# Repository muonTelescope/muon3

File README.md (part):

# Muon3: a networked cosmic-ray muon station

**In plain English:** muons from cosmic-ray showers pass through us all the time. A plastic scintillator tile gives off a
tiny flash when one crosses it. A silicon photomultiplier (SiPM) turns that flash into a current pulse, and a small board
counts pulses that arrive in several stacked tiles at once. Muon3 is the next-generation station for the Georgia State
University [gLOWCOST](https://cosmic.gsu.edu/) network: cheap, identical detectors in classrooms and labs that log how the
muon rate follows air pressure, temperature and space weather.

A station is **four decommissioned sPHENIX inner-HCal tiles** (Hamamatsu S12572-33-015P SiPMs), stacked 100 mm apart in a
printed ABS frame. Each tile carries one wavelength-shifting fiber in a closed loop, under a reflective coating and a
light-tight wrap. **One 337 × 40 mm, 4-layer, USB-powered board**, assembled by JLC on one side, stands behind the tiles with
its long axis along the stack: its four channel cells sit right behind the four SiPM boards, so the four micro-coax cables are
short (57 mm) and identical. The hub (USB-C, ESP32, bias supply, pressure/temperature) sits between tiles 1 and 2. A printed
three-segment case covers the board. There is no display: the station reports over USB and Wi-Fi.

| | |
|---|---|
|  |  |

## Contents

0. [Quick start](#quick-start) · [How a muon becomes a count](#how-a-muon-becomes-a-count) · 1. [What you get](#1-what-you-get) · 2. [Bill of materials and cost](#2-bill-of-materials-and-cost) · 3. [Install it: step by step](#3-install-it-step-by-step)
· 4. [Test and calibrate](#4-test-and-calibrate) · 5. [The 12 tile shapes](#5-the-12-tile-shapes) · 6. [The electronics](#6-the-electronics)
· 7. [Simulated performance](#7-simulated-performance) · 8. [Regenerate the design files](#8-regenerate-the-design-files)
· 9. [The bench test board](#9-the-bench-test-board) · 10. [Wright-style detector layouts](#10-wright-style-detector-layouts)
· 11. [Design notes, open questions, repository map](#11-design-notes-open-questions-repository-map)

---

## Quick start

```bash
git clone git@github.com:muonTelescope/muon3.git && cd muon3/hw
bun run parts && bun run build && bun run drc      # the board: Gerbers, BOM, CPL in hw/out/ (section 8 lists the tools to install first)
freecadcmd case/case.py                            # the three case segments
TILE=6 freecadcmd case/assembly.py                 # the frame, plate and tile stack for tile shape 6 (any of 1–12)
python tools/station_test.py board                 # factory test over USB, once a board is assembled
```

## How a muon becomes a count

1. **Light.** A cosmic-ray muon crossing a 7 mm polystyrene tile deposits about 1.5 MeV and makes some 13 000 scintillation photons
   (blue, 420 nm). About 2 500 of them are absorbed by the 1 mm wavelength-shifting fiber in the tile and re-emitted at 476 nm (green);
   light trapped in the fiber travels both ways round the closed loop to the SiPM. Of the order of 150 photons reach the SiPM and about
   35 are detected (PDE 25 %): the **photoelectrons (p.e.)**.
2. **Current.** The S12572 SiPM, biased at 53–83 V, turns each p.e. into a fast current pulse (gain about 2.3 × 10⁵). The bias comes from
   the MC34063 boost converter on the board and reaches the SiPM over the same micro-coax that carries the signal back.
3. **Voltage.** A transimpedance amplifier (OPA356, 33 kΩ) gives 5.8 mV per p.e., so a mean muon makes a 209 mV pulse about 370 ns long.
4. **Decision.** A comparator (LMV7219) fires when the pulse passes a threshold set by a DAC: 29 mV, 5 p.e., rejects dark counts (single
   p.e.) and keeps essentially every muon that crosses the tile.
5. **Count.** The ESP32-S3 time-stamps each edge (MCPWM capture, 12.5 ns) and counts singles (PCNT); coincidences of the four tiles are
   formed in firmware, together with pressure and temperature (BME280), and sent over Wi-Fi or USB. The muon rate follows air pressure,
   temperature and space weather: that is what the gLOWCOST network logs. `sim/python/coincidence_rates.py` computes the coincidence and
   accidental rates; `sim/python/sipm_to_tot.py` maps SiPM charge to time over threshold.

---

## 1. What you get

- **Identical channels.** Channel 0 is placed and routed once; cells 1–3 are exact copies at a 100 mm pitch (copper identical
  to 2 µm, checked on every build with `hw/tools/cell_identity.py`). The pitch is the tile pitch, so cell *k* is behind tile *k*.
- **The SiPM bias never leaves the case.** Each tile's micro-coax plugs into a U.FL jack inside the case.
- **External antenna.** An ESP32-S3-WROOM-1U-N16R8 sends its Wi-Fi/BLE through a U.FL pigtail to a flat antenna on the lid.
- **Fits every tile.** All 12 inner-HCal tile shapes, from the 121 mm wide, nearly rectangular tile 01 to the 403 mm
  parallelogram tile 12, get a frame and a fiber loop generated from their outline.
- **Self-testing.** The board tests itself over USB in 2 minutes (nothing plugged in), and calibrates each tile's gain from its
  own dark counts.

```text
 tile ─ micro-coax ─► U.FL in the case (shell = bias via 47 kΩ) ─► OPA356 TIA (33 kΩ ‖ 2.7 pF) ─► LMV7219 ─► HIT_n ─► ESP32-S3
   ×4 (identical cells)           ▲                               ▲ VREF (DAC B·A)             ▲ VTH_n (DAC A)      PCNT + MCPWM
             MC34063 boost → 10 k / 1 µF RC ─ HV (53–83 V) ◄─ HV_TRIM (DAC B·B) ◄──────────────────────────── HV_EN
                         └──────────── HV_MON (÷ 27.7) ────────────────────────────────────────────────────► ADC
 INJ (GPIO) ─ 10 k/1.1 k ─ 1 pF into each input: 0.33 pC = 9 p.e. self-test
 BME280 (slotted thermal island, ≥ 20 mm from any input) · SC7A20H tilt · USB-C 5 V → AMS1117 3V3 + TLV75733 3V3A
```

---

## 2. Bill of materials and cost

### Board (JLC assembles it; 155 parts, 45 lines)

Upload `hw/out/muon3-gerbers.zip`, `hw/out/bom.csv` and `hw/out/cpl.csv` to JLCPCB: **4 layers, 1.6 mm, top-side assembly only**,
337 × 40 mm. Parts come from LCSC; the full list is [`hw/parts/INDEX.md`](hw/parts/INDEX.md).

| Line | Part | Per board | Share |
|---|---|---|---|
| BME280 (pressure, temperature) | C92489 | $4.46 | 27 % |
| ESP32-S3-WROOM-1U-N16R8 (Wi-Fi, BLE, U.FL antenna connector) | C3013946 | $4.10 | 24 % |
| MCP4728 DAC × 2 | C478093 | $3.06 | 18 % |
| OPA356 TIA × 4 | C183100 | $1.83 | 11 % |
| LMV7219 comparator × 4 | C20613263 | $0.99 | 6 % |
| U.FL jack × 4, SC7A20H, AMS1117, MC34063, TLV75733 | | $0.95 | 6 % |
| the other 34 lines, mostly 0402/0805 passives | | $1.19 | 7 % |

**Cost at 100 boards (importer: GSU): parts $16.58 + PCB $6.19 + JLC assembly $1.32 = $24.08 ex-works, $35.57 landed in the US**
($105.57 per board for the two Berlin prototypes). The PCB price is an estimate ($0.045 per cm² of 4-layer board, 135 cm² here): get a
quote. Cheaper variants (saves about $6.3 per board, landed $35.6 → $26.4): BME280 → SPA06-003 (same package, pressure + temperature,
$0.51), drop the second MCP4728 (fixed VREF divider, PWM HV trim), ESP32 N4 module, drop the tilt sensor, two extended parts →
basic parts. Not worth it: a 2-layer board (saves $1.50, loses the ground plane), dropping the analog LDO, cheaper op-amps.

### Mechanics and cables (you print and buy these)

| Part | Qty | How |
|---|---|---|
| Corner clip (ABS, 12.4 mm thick, 8.0 mm slot, M6 hole) | 16 | printed, flat |
| Spacer tube (Ø 12 / Ø 6.4) | 18 (6 × 87.6 mm, 12 × 4.8 mm) | printed; the long ones can be aluminium tube |
| Back plate bar (one piece for tiles 1–11; two halves + a splice plate for tile 12) | 3 | printed, lying on its back |
| Case base + lid, segments A (71 mm), B (200 mm), C (71 mm) | 3 + 3 | each flat |
| M6 threaded rod, about 345 mm | 4 | cut from 1 m stock |
| M6 nut + washer | 8 + 8 | |
| M3 × 5.7 heat-set insert | 13 (lid) + 10 (plate bars) (+ 12 for the tile-12 splices) | pressed in with a soldering iron |
| M3 × 12 socket-head screw (ISO 4762) | 13 | lid, through the board's edge holes |
| M3 × 6 socket-head screw (ISO 4762) | 10 (+ 12 for the tile-12 splices) | case floor to plate bars |
| U.FL to U.FL micro-coax, Ø 1.13 mm, 70 mm | 4 | tile SiPM board to station board; four equal lengths |
| 2.4 GHz FPC antenna, 35 × 7 mm, with U.FL pigtail | 1 | sticks in the lid recess |
| Tile wrap: 100 µm Al foil, 30 µm cling film, 100 µm black vinyl, epoxy (EPO-TEK 301 class) | 4 tiles | plus the tile's 50 µm painted reflector |
| 4 decommissioned sPHENIX inner-HCal tiles with their fibers, SiPMs and SiPM boards (from GSU) | 4 | of one shape |

Print in ABS at 0.2 mm layers, 4 perimeters, 30 % infill, 100 °C bed, enclosure closed. The longest parts are case segment B
(206 mm) and the plate bars (up to 212 mm): both fit a 220 mm bed.

---

## 3. Install it: step by step

All M3 joints are **socket-head screws into heat-set inserts** (no nuts, no glue). Press the inserts in first: hold each on its hole
with a soldering iron at 220–240 °C and push it flush. Everything below is generated for your tile shape (1–12): run the commands in
[section 8](#8-regenerate-the-design-files) with `TILE=<n>` to get the exact STL/STEP files.

### Step 0: order and print

1. Order the board (section 2). Order or print the parts (`hw/out/case/case_{base,lid}_{A,B,C}.stl`, and the clips, spacers and bars
   from `hw/out/assembly/tileNN/`).
2. Check the board when it arrives: `python hw/tools/station_test.py board` (section 4).

### Step 1: the tiles

The tile is a slab of extruded polystyrene with **one Kuraray Y11 fiber laid in a closed loop**: both ends leave the flat SiPM edge
side by side, each runs through an S-bend of 25 mm radius onto a leg, the two legs run down the tile and a semicircle closes the
loop near the far edge. Over the tile go the **50 µm painted reflector** and the **wrap: 100 µm aluminium foil, 30 µm cling film,
100 µm black vinyl**, each following the tile's outline and open only where the coupler sits (Aidala et al., IEEE TNS 65 (2018),
Table II and Fig. 6). Tiles 01, 06 and 12, bare, with the fiber in its groove and the coupler and SiPM board on the SiPM edge:

The same tile with its layers lifted off one by one (reflector, foil, cling film, vinyl):

1. Lay the fiber in its groove (epoxy) and cut and polish both ends flush with the SiPM edge.
2. Put on the reflector and the wrap (foil, cling film, vinyl), open at the coupler.
3. Glue the coupler block (16 × 6 × 8 mm, black ABS) on the SiPM edge over the two fiber ends, with the SiPM board and its U.FL
   jack behind it. Both ends, 1.2 mm apart, face the one 3 × 3 mm SiPM across a 0.75 mm air gap.

### Step 2: the frame

Slide the four rods through the bottom clips, add the nuts, then build up: spacer, tile in its four corner clips, spacer, next tile.
The four clips of a tile clamp its corners in an 8.0 mm slot; the tile is never drilled. The rods sit 8.5 mm outside each corner, so
they never touch the scintillator.

### Step 3: the back plate

A bar replaces the back-rod spacer between tiles 0/1, 1/2 and 2/3. Each bar's two sleeves slide onto the back rods (bars are at
z = 50, 150 and 250 mm, clear of the SiPM boards at z = 0, 100, 200, 300, so the coax passes between them). For tile 12 each bar is
two halves joined by a splice plate on the front face (4 × M3 × 6).

### Step 4: the electronics

Press the inserts into the three case bases. Drop the board onto the bosses of the bases (the board's underside has no parts; the
heads of the floor screws sit in the 4.6 mm gap under it), close the three lids (13 × M3 × 12) and screw each segment's base to the
bars (10 × M3 × 6). The segments join at the bars (board x = 68.5 and 268.5 mm). The USB-C opening is on the far long wall, the
BME280 vent beside it.

### Step 5: cables and antenna

Plug a 70 mm micro-coax onto each tile's SiPM board, route it out to the case wall, and click its other plug onto the board's jack
through the notch in the lid skirt, then lay it in the zip-tie bridge on the wall. All four cables are identical. Stick the FPC antenna
in the lid recess and click its pigtail onto the ESP32 module's U.FL through the lid hole.

### Sections (tile 01)

Through the SiPM edge (scintillator with its coating and wrap, fiber in its groove, coupler, SiPM, board, plug) and through the case
at the hub (lid, board on its 4.6 mm standoffs, base, plate bar):

| | |
|---|---|
|  |  |

The widest shape (tile 12), from the back:

### Case and plate details

- **Three printed segments** (71, 200, 71 mm, each with a base and a lid, split at the board mid-plane) because the board is 337 mm long;
  the joints sit on the plate bars. The lid screws sit 7 mm either side of a joint so that no boss is cut.
- **Coax entry.** A 1.8 × 2.4 mm notch in the lid skirt above each U.FL takes the micro-coax; a small zip-tie bridge on the wall takes the
  strain off the plug. The bias on the U.FL shells stays inside the closed case.
- **BME280 chamber.** Ribs above and below the island (stopping 0.15 mm short of the board), vented to room air through eight 1.6 mm
  slots in the far wall. **Hot side:** eight 1.6 × 14 mm chimney slots in the floor and lid over the ESP32 and AMS1117.
- **External antenna.** A Ø 3.2 mm hole in the lid over the module's U.FL jack passes the pigtail to a 35 × 7 × 0.7 mm recess on the
  lid's outer face, along the far edge.
- **Mounting.** Ten Ø 3.4 mm holes in the base floors take M3 × 6 screws into the bars' inserts (two per segment per bar).

### Step 6: install

Put the stack where it will stay (tiles horizontal). Plug a USB-C power source into the hub's USB-C port (a bank that can deliver
the station's 40–120 mA continuously: many switch off below 50–100 mA). Give it Wi-Fi credentials over the USB serial port.
*(The firmware is not written yet: its USB line protocol is specified in `hw/tools/station_test.py`.)*

---

## 4. Test and calibrate

Every board is tested and calibrated by the ESP32 itself, driven from a laptop over USB:

```bash
python hw/tools/station_test.py board          # factory test: nothing plugged in, about 2 min
python hw/tools/station_test.py tile --ch 0    # per tile, at installation: about 10 min per channel
```

No scope or fixture is needed. The probe row (22 pads, 2.54 mm pitch, far long edge at the right-hand end of the board) and the
TIA/GND scope pair in each channel cell are for diagnosing a board that fails. The station has one status LED (next to the BOOT
button, through a light pipe in the lid): the firmware is specified to blink fast during the 10 s self-test, slowly while counting and
to stay on in a fault.

**How it works.** Each channel has a 1 pF injection capacitor driven from the INJ GPIO through a 10 k / 1.1 k divider: each edge puts
0.33 pC on the TIA input, which is 9 photoelectrons (p.e.). The firmware sweeps the threshold DAC and counts HIT pulses: the threshold
at which half the injected pulses still fire measures the whole chain at once. The bias checks itself through HV_MON (HV ÷ 27.7). The
tile calibrates its own gain: in the dark a SiPM fires single p.e., the count rate against threshold falls in a staircase, and the step
spacing is 1 p.e. (set the bias so it is 5.8 mV, then put the threshold at 5 p.e. = 29 mV). The same staircase, repeated every few
minutes, is the running gain servo.

### Factory test (`board`)

| Step | What the firmware does | Pass | Source |
|---|---|---|---|
| 1 | Scan both I2C buses | BME280 0x76, SC7A20H 0x19, MCP4728 0x60 on I2C0 and I2C1 | design |
| 2 | Read BME280 pressure | 850–1090 hPa | — |
| 3 | HV_EN low, read HV_MON | 2.5–5.5 V (USB 5 V minus the boost diode; not 0 V) | [SIM] ≈ 4 V |
| 4 | HV_EN high, TRIM = 0 / 1.0 / 2.048 V | 80–86.5 V / 65.5–71.5 V / 50–56 V | [SIM] 83.0 / 68.3 / 52.9 V |
| 5 | Store HV(TRIM) line; leave the bias at TRIM 2.048 V and HV_EN low | — | — |
| 6 | Per channel: VTH staircase with no injection | noise edge ≤ 8 mV below VREF | [SIM] < 3 mV |
| 7 | Per channel: VTH staircase with INJ pulses, 50 % point | 85–135 mV below VREF | [SIM] 109 mV |
| 8 | Join the test access point, read RSSI (the external antenna must be on the lid) | ≥ −65 dBm at 2 m | first prototype |

*Simulated scope screens (what you should see on the probe points): ① injection with nothing plugged in: a 109 mV dip follows each INJ
edge and HIT0 fires on the negative one. ② With a tile and coax attached the charge shares the SiPM's 320 pF and the dip halves (55 mV).
③ A single dark pulse (5.8 mV, shown ×10) and a mean muon (36 p.e., 209 mV, time over threshold ≈ 370 ns). ④ The bias power-up on
HV_MON: ≈ 4 V until HV_EN goes high at 10 ms, then 60–90 ms to settle.*

### Per-tile calibration (`tile`)

1. Attach the tile and close the light-tight wrap. Set the bias to the tile's operating voltage V_op (from the Hamamatsu/GSU sheet);
   the firmware closes the loop on HV_MON using the stored HV(TRIM) line.
2. **Staircase.** Sweep VTH 1–40 mV below VREF, 200 ms per step. The peaks in −d(log rate)/dVTH sit between p.e. steps; their
   spacing is the 1 p.e. amplitude.
3. If the step is not 5.8 mV, move V_op by ΔV = (5.8 / step − 1) · (V_op − V_bd) and repeat.
4. Threshold = 5 p.e.; store `pe_n`, `vth_n` and V_op in NVS.
5. With the tiles stacked, run the coincidence plateau: V_op ± 1 V in 0.25 V steps, 5 min each. The rate should be flat within its
   statistical error. Expect a few counts per minute for a 12 × 19 cm tile (cosmic muons: about 1 per cm² per minute × the geometric
   acceptance). Measure each tile's efficiency with the coincidence method (three tiles fire, does the fourth?).

### Diagnosing a failed board

| Probe (row, left → right) | Expect |
|---|---|
| GND · 5V · 3V3 · 3V3A | 0 · 4.8–5.2 · 3.25–3.35 · 3.25–3.35 V |
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
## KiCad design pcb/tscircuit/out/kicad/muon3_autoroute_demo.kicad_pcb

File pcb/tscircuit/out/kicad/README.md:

# Muon3 tscircuit → KiCad export

Generated by `bun run export:kicad` from `muon3_placement.tsx`.

## Files

| File | Use |
|------|-----|
| `muon3_tscircuit_placement.kicad_pro` | Open in KiCad 9+ as **placement reference** |
| `muon3_tscircuit_placement.kicad_pcb` | Footprints, keepouts, zone silkscreen from tscircuit |
| `muon3_tscircuit_placement.kicad_sch` | Minimal schematic (placement anchors only) |
| `../placement_positions.json` | Component XY for manual placement in production PCB |
| `../placement_positions.csv` | Same table as CSV |

## How to use with production `muon3.kicad_pro`

1. Open **this** project to inspect recommended placement / keepouts.
2. Open **`../../muon3.kicad_pro`** (hierarchical production sheets).
3. Place production footprints using `placement_positions.csv` coordinates
   (KiCad columns), or run `bun run sync:zones` to stamp zone fences into
   the production board outline.
4. For autorouted demo nets → KiCad, run `bun run autoroute` then re-export.

**Do not** overwrite production hierarchical schematics with this export.

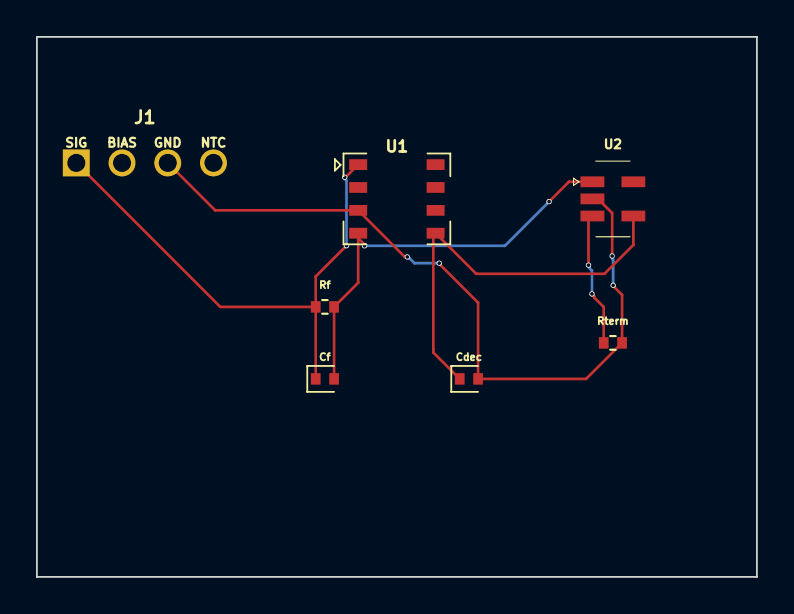
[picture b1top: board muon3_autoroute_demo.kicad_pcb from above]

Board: 2 copper layers, 40.0 x 30.0 mm, 7 parts (0 on the bottom side), 5 nets.

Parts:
Cdec: 100nF; capacitor_0402
Cf: 1pF; capacitor_0402
J1: chip_pinrow4
Rf: 4.99kΩ; resistor_res0402
Rterm: 49.9Ω; resistor_res0402
U1: chip_dfn8
U2: chip_sot23_5

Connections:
.J1 > .pin1 to .U1 > .pin1: Cf.1, J1.1, Rf.1, U1.1
.Rf > .pin2 to .U1 > .pin4: Cf.2, Rf.2, U1.4, U2.1
.U2 > .pin3 to .Rterm > .pin1: Rterm.1, U2.3
GND: Cdec.2, J1.3, Rterm.2, U1.3, U2.2
VCC_3V3: Cdec.1, U1.5, U2.4

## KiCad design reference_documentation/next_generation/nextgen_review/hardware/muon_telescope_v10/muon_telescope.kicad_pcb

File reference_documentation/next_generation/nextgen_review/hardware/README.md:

# SiPM Muon Telescope — KiCad Project (KiCad 10)

Generated 2026-06-11. Four hierarchical sheets implementing the simulated TIA front-end design
(see the accompanying simulation report): 4× SiPM → OPA858 TIA → TLV3601 → iCE40UP5K-SG48,
TPS61170 HV boost + π filter + DAC trim + ADC readback, DAC7578 thresholds, BME280, W25Q128
config flash, TCXO, GNSS-module and nRF9151-carrier headers.

## Opening in KiCad 10

Open `muon_telescope_v10/muon_telescope.kicad_pro`. The schematic files are written in the
20250114 s-expression format with generator_version 9.0 — the exact format the KiCad 10.0
release ships its own demo projects in. KiCad 10 opens it natively (the official migration
path); on first save it re-stamps the files to the current 20260306 format. Every s-expression
token used was checked against KiCad 10.0's parser keyword list (eeschema/schematic.keywords,
branch 10.0), and the grammar was pattern-matched against reference files from the 10.0 source
tree.

`muon_telescope_v7/` contains a byte-equivalent-structure twin in KiCad 7 format. It exists
because this project was machine-generated and validated headlessly with kicad-cli 7.0.11:
SVG/PDF plots of all four sheets plus a full netlist export, with the connectivity of every
critical net checked programmatically (TIA feedback loops, all four CMPx→FPGA pins, shared
VBOT, DAC routing, HV trim/readback, PPS, config-flash SPI, nRF SPI, 1V2 core). The v10 set is
generated from the identical structure, so the electrical verification carries over.

## First steps after opening

1. Run ERC. Global-label connectivity is used throughout (machine-generated layout); expect
   only style-level warnings.
2. Annotation is pre-assigned and collision-free; re-annotate only if you restructure.
3. Tidy label positions to taste — symbols are placed on grid but some labels overlap.

## Libraries

- `muon_parts.kicad_sym` — project library, all symbols used. Also embedded in each sheet, so
  the schematics are self-contained.
- `JLCPCB-Kicad-Library/` — bundled subset (symbols + footprints) of
  https://github.com/CDFER/JLCPCB-Kicad-Library (MIT). sym-lib-table and fp-lib-table already
  point at it via ${KIPRJMOD}. Re-clone the upstream repo for 3D models and live stock data.

## Sourcing status (read before ordering)

CDFER basic/preferred parts with LCSC numbers embedded in symbol fields:
all 0402/0603 R and C values, BAV99 (C2500), SS510B 100V Schottky (C7420368), 100µH filter
inductor (C68035), AMS1117-3.3 (C6186), BME280 (C92489), W25Q128JVSIQ (C97521).

Pinout-verified from official KiCad library or TI datasheets, LCSC ID to confirm at order time
(extended parts): OPA858 (WSON-8), TLV3601 (SOT-23-5: 1=OUT 2=VEE 3=IN+ 4=IN− 5=VCC, TI
SNOSDB1E), TPS61170 (VSON-6: 1=FB 2=COMP 3=GND 4=SW 5=CTRL 6=VIN, TI SLVS789D), DAC7578
(TSSOP-16), iCE40UP5K-SG48ITR (QFN-48).

Marked VERIFY in-schematic before ordering: XC6206P122 1.2 V LDO pinout and LCSC number;
TCXO footprint/pinout vs the exact part chosen; the two placeholder LCSC numbers on
0402 1µF / 0603 10µF; DAC7578 I²C address for ADDR0=GND; iCE40 VPP_2V5-from-3V3 against the
current Lattice datasheet; all HV-node capacitors must be ≥50 V (C0G/film on HV_QUIET).

## Design notes carried from simulation

DC-coupled anode readout: SiPM anode sits at the TIA virtual ground (VBOT, 2.40 V), cathode at
HV_QUIET — no input coupling cap, no undershoot. HV ≈ VBOT + Vbr + Vov: ~32.4 V for
MicroFC-30035 as drawn; for Hamamatsu S13360 (~58 V) replace the boost stage, filter unchanged.
Rf=2 kΩ 1%, Cf=2.2 pF C0G → 24.4 mV/p.e., 52 MHz, 3 p.e. threshold = 74 mV below baseline.
Comparator output idles HIGH, pulses LOW (falling edge = event), matching firmware convention.

## Layout-critical items

Rf/Cf at the OPA858 pins, no plane under summing nodes; boost hot loop compact and far from
the four INA nodes; comparator output routing away from analog inputs; star HV_QUIET
distribution after C12; thermal pads (OPA858 pin 9, TPS61170 pin 7, iCE40 pin 49) to GND.

## Regenerating

`python3 gen_sch.py v9` (KiCad-10-ready) or `python3 gen_sch.py v7` (kicad-cli-7-validatable).
gen_symbols.py holds all pin maps with their provenance in comments.

## PCB (muon_telescope.kicad_pcb)

108 x 86 mm, 4-layer: F.Cu signal | In1 solid GND | In2 +3V3 plane | B.Cu GND pour.
Placement complete and DRC-clean (0 clearance / courtyard / hole violations); routing is
intentionally left open — unconnected-net DRC entries are the ratsnest. The board file is
KiCad 7 format; KiCad 10 opens and migrates it like the schematics.

Grounding / noise architecture baked into the file:
- ONE continuous ground domain. No split planes anywhere — return currents cannot be forced
  around a slot, which is the classic ground-loop generator. Partitioning is by placement.
- 31 GND stitching vias on a 9 mm grid keep F.Cu / In1 / B.Cu grounds at the same potential
  at RF, preventing the pour islands from becoming patch antennas.
- Per-channel rule areas (no copper pour, In1+In2+B.Cu) under each TIA summing node:
  keeps parasitic capacitance off the Cf node and leakage paths off the femtocoulomb input.
- Boost quarantine: TPS61170 hot loop bottom-right, >40 mm from the nearest summing node;
  In2 under the entire boost area is GND (priority fill), denying the 3V3 plane any
  capacitive pickup from the switch node directly beneath it.
- U.FL per channel at the board edge: CENTER = anode signal, SHIELD = HV bias. The shield is
  AC-grounded by C1 within ~6 mm of the connector, so it shields normally while DC-carrying
  the bias - one coax per SiPM, minimal loop area. Both shield legs of the BWIPX footprint
  are netted (the upstream CDFER symbol leaves pad 3 floating - fixed here).
- HV netclass (0.5 mm clearance, pattern HV_* + BOOST_SW) is defined in the .kicad_pro.

Routing order suggestion: (1) per-channel input: U.FL center -> R2 -> summing node -> OPA858
pin 3, with Rf/Cf to the FB pin, shortest possible, F.Cu only; (2) TIA -> comparator -> R5;
(3) CMPx to FPGA as spaced single-ended lines over solid In1; (4) HV_QUIET from C12 along the
bottom/left perimeter to the four R1s (DC, filtered - length is free); (5) boost hot loop
L1/U10/D10/C10 tight first, before anything else near it; (6) supplies last via In2 + drops.
Pad-local notes: thermal pads of U10/U101..U131/U3 need via farms to In1.

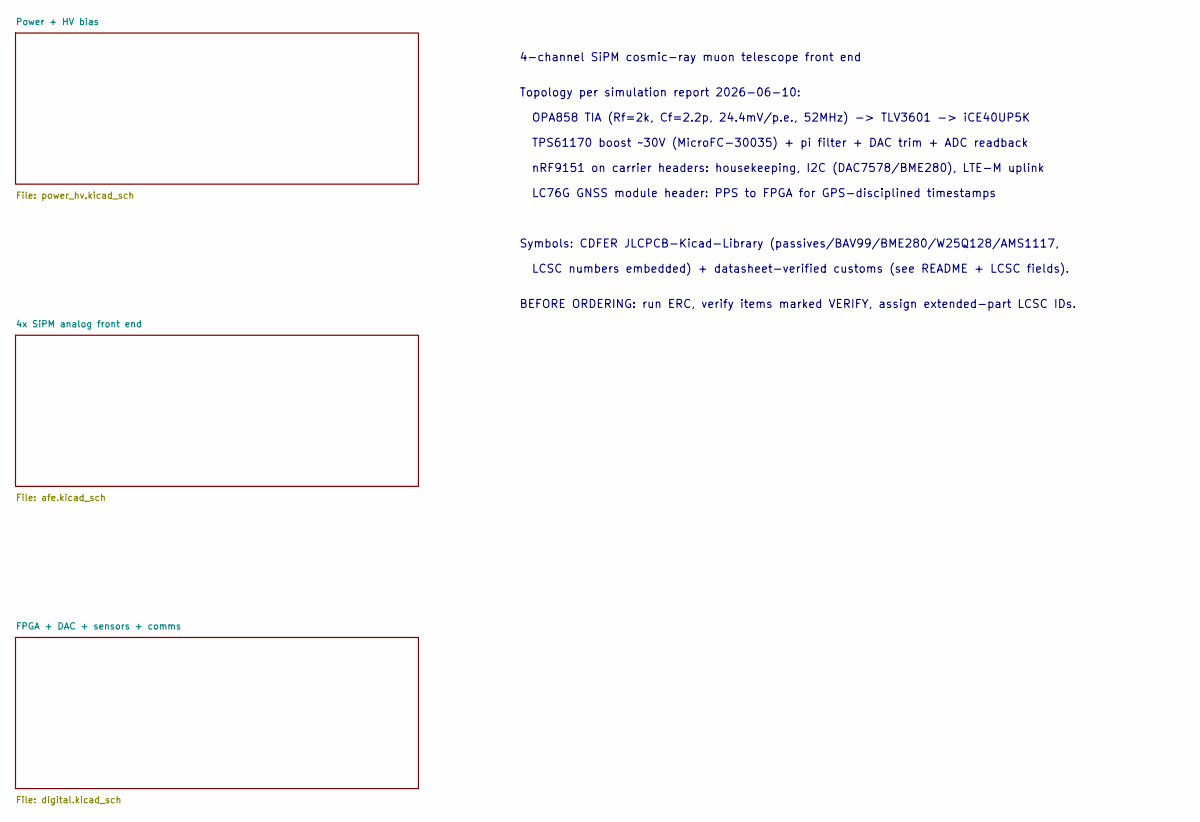
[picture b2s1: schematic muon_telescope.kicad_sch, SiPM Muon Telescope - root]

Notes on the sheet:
4-channel SiPM cosmic-ray muon telescope front end
Topology per simulation report 2026-06-10:
OPA858 TIA (Rf=2k, Cf=2.2p, 24.4mV/p.e., 52MHz) -> TLV3601 -> iCE40UP5K
TPS61170 boost ~30V (MicroFC-30035) + pi filter + DAC trim + ADC readback
nRF9151 on carrier headers: housekeeping, I2C (DAC7578/BME280), LTE-M uplink
LC76G GNSS module header: PPS to FPGA for GPS-disciplined timestamps
Symbols: CDFER JLCPCB-Kicad-Library (passives/BAV99/BME280/W25Q128/AMS1117,
LCSC numbers embedded) + datasheet-verified customs (see README + LCSC fields).
BEFORE ORDERING: run ERC, verify items marked VERIFY, assign extended-part LCSC IDs.

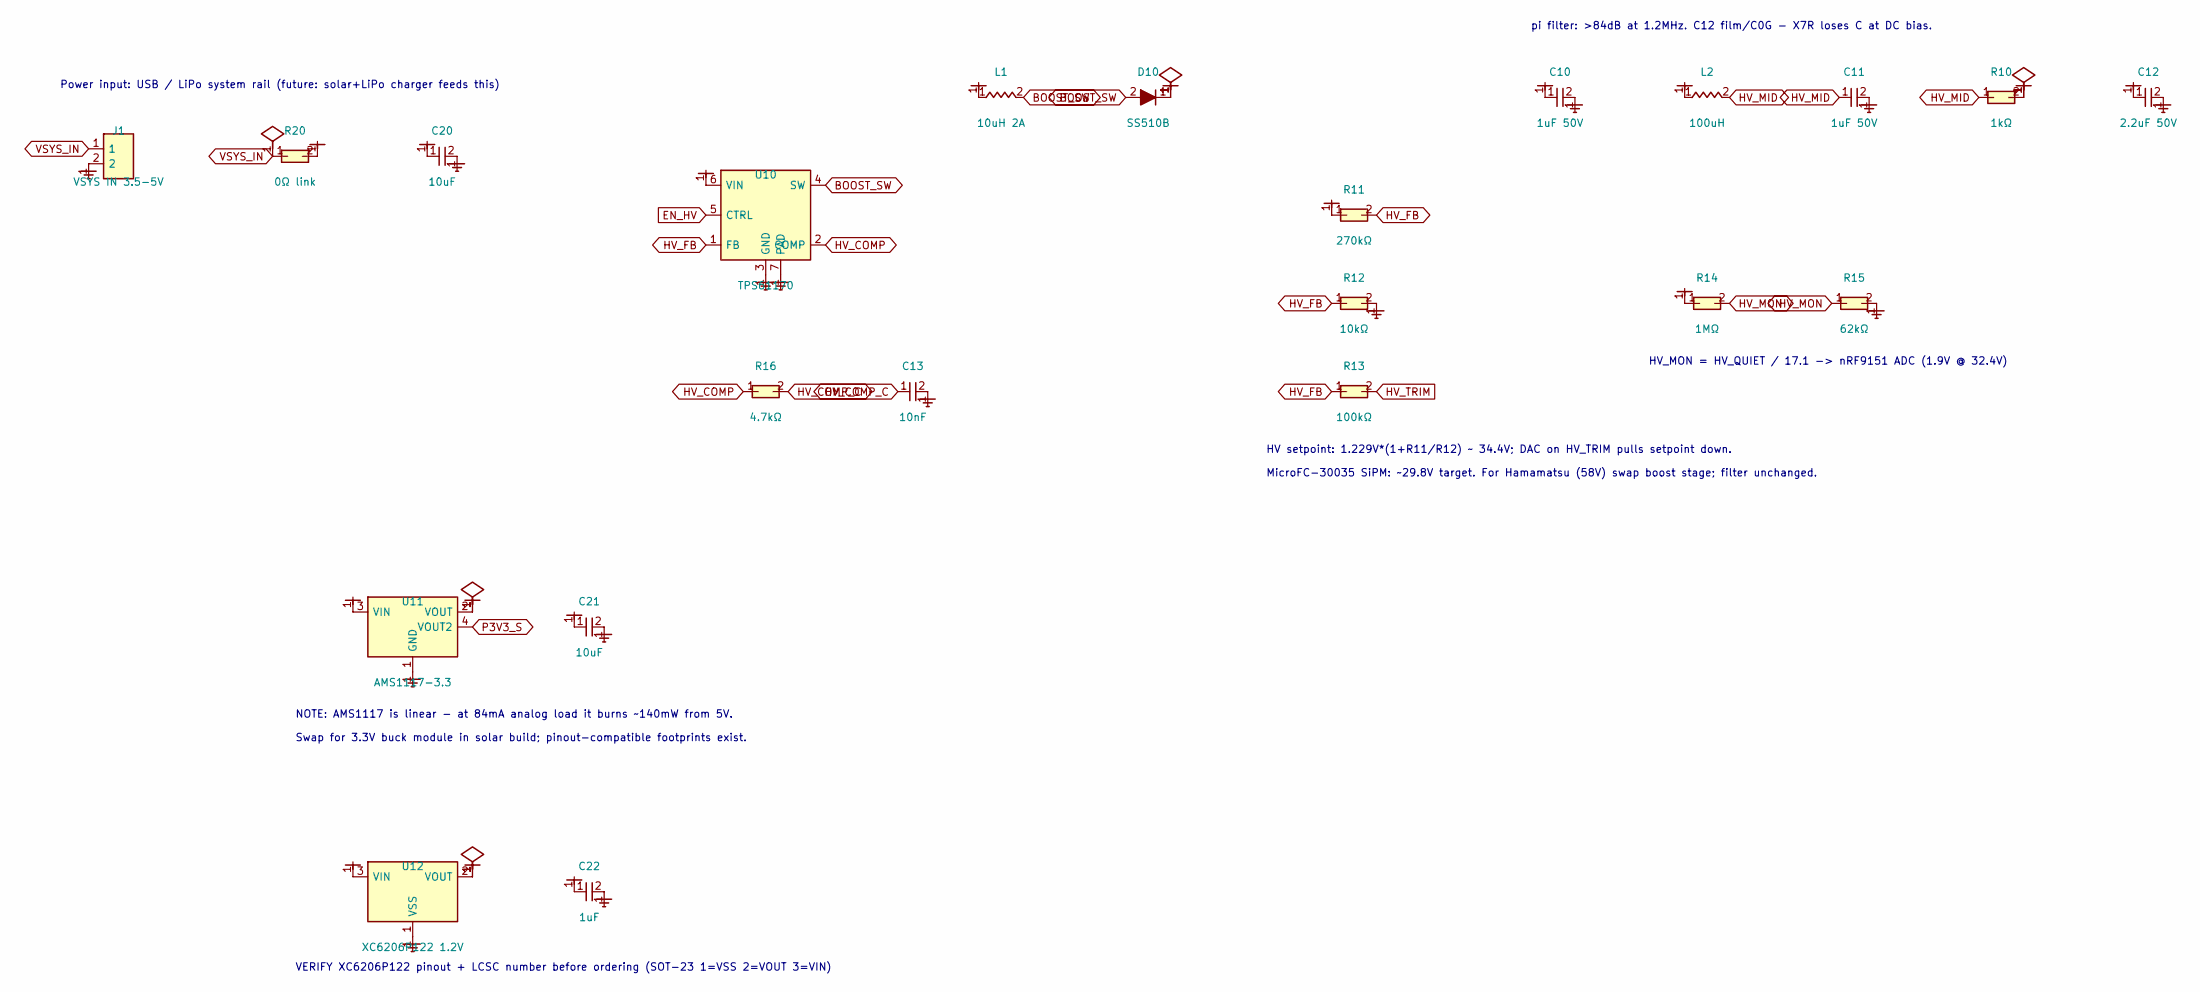
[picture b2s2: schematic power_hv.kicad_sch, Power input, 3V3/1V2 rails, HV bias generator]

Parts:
C10, C11: 1uF 50V; C_1206
C12: 2.2uF 50V; C_1206
C13: 10nF; C_0402; LCSC C15195
C20, C21: 10uF; C_0603; LCSC C19702
C22: 1uF; C_0402; LCSC C52923
D10: SS510B; D_SMB; LCSC C7420368
J1: VSYS IN 3.5-5V; PinHeader_1x02_P2.54mm_Vertical
L1: 10uH 2A; L_Taiyo-Yuden_NR-40xx
L2: 100uH; L_0805; LCSC C68035
R10: 1kΩ; R_0402; LCSC C11702
R11: 270kΩ; R_0603; LCSC C22965
R12: 10kΩ; R_0402; LCSC C25744
R13: 100kΩ; R_0402; LCSC C25741
R14: 1MΩ; R_0402; LCSC C26083
R15: 62kΩ; R_0603; LCSC C23221
R16: 4.7kΩ; R_0402; LCSC C25900
R20: 0Ω link; R_0402; LCSC C25076
U10: TPS61170; WSON-6-1EP_2x2mm_P0.65mm_EP1x1.6mm
U11: AMS1117-3.3; SOT-223-3_L6.5-W3.4-P2.30-LS7.0-BR; LCSC C6186
U12: XC6206P122 1.2V; SOT-23-3_L2.9-W1.6-P1.90-LS2.8-BR

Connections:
+1V2: C22.1, U12.2 (VOUT); also elsewhere on the board
+3V3: C21.1, U11.2 (VOUT), U12.3 (VIN); also elsewhere on the board
BOOST_SW: D10.2 (A), L1.2, U10.4 (SW)
EN_HV: U10.5 (CTRL); also elsewhere on the board
GND: C10.2, C11.2, C12.2, C13.2, C20.2, C21.2, C22.2, J1.2, R12.2, R15.2, U10.3 (GND), U10.7 (PAD), U11.1 (GND), U12.1 (VSS); also elsewhere on the board
HV_COMP: R16.1, U10.2 (COMP)
HV_COMP_C: C13.1, R16.2
HV_FB: R11.2, R12.1, R13.1, U10.1 (FB)
HV_MID: C11.1, L2.2, R10.1
HV_MON: R14.2, R15.1; also elsewhere on the board
HV_QUIET: C12.1, R10.2, R14.1; also elsewhere on the board
HV_RAW: C10.1, D10.1 (K), L2.1, R11.1
HV_TRIM: R13.2; also elsewhere on the board
P3V3_S: U11.4 (VOUT2)
VSYS: C20.1, L1.1, R20.2, U10.6 (VIN), U11.3 (VIN); also elsewhere on the board
VSYS_IN: J1.1, R20.1

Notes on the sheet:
Power input: USB / LiPo system rail (future: solar+LiPo charger feeds this)
HV setpoint: 1.229V*(1+R11/R12) ~ 34.4V; DAC on HV_TRIM pulls setpoint down.
MicroFC-30035 SiPM: ~29.8V target. For Hamamatsu (58V) swap boost stage; filter unchanged.
pi filter: >84dB at 1.2MHz. C12 film/C0G - X7R loses C at DC bias.
HV_MON = HV_QUIET / 17.1 -> nRF9151 ADC (1.9V @ 32.4V)
NOTE: AMS1117 is linear - at 84mA analog load it burns ~140mW from 5V.
Swap for 3.3V buck module in solar build; pinout-compatible footprints exist.
VERIFY XC6206P122 pinout + LCSC number before ordering (SOT-23 1=VSS 2=VOUT 3=VIN)

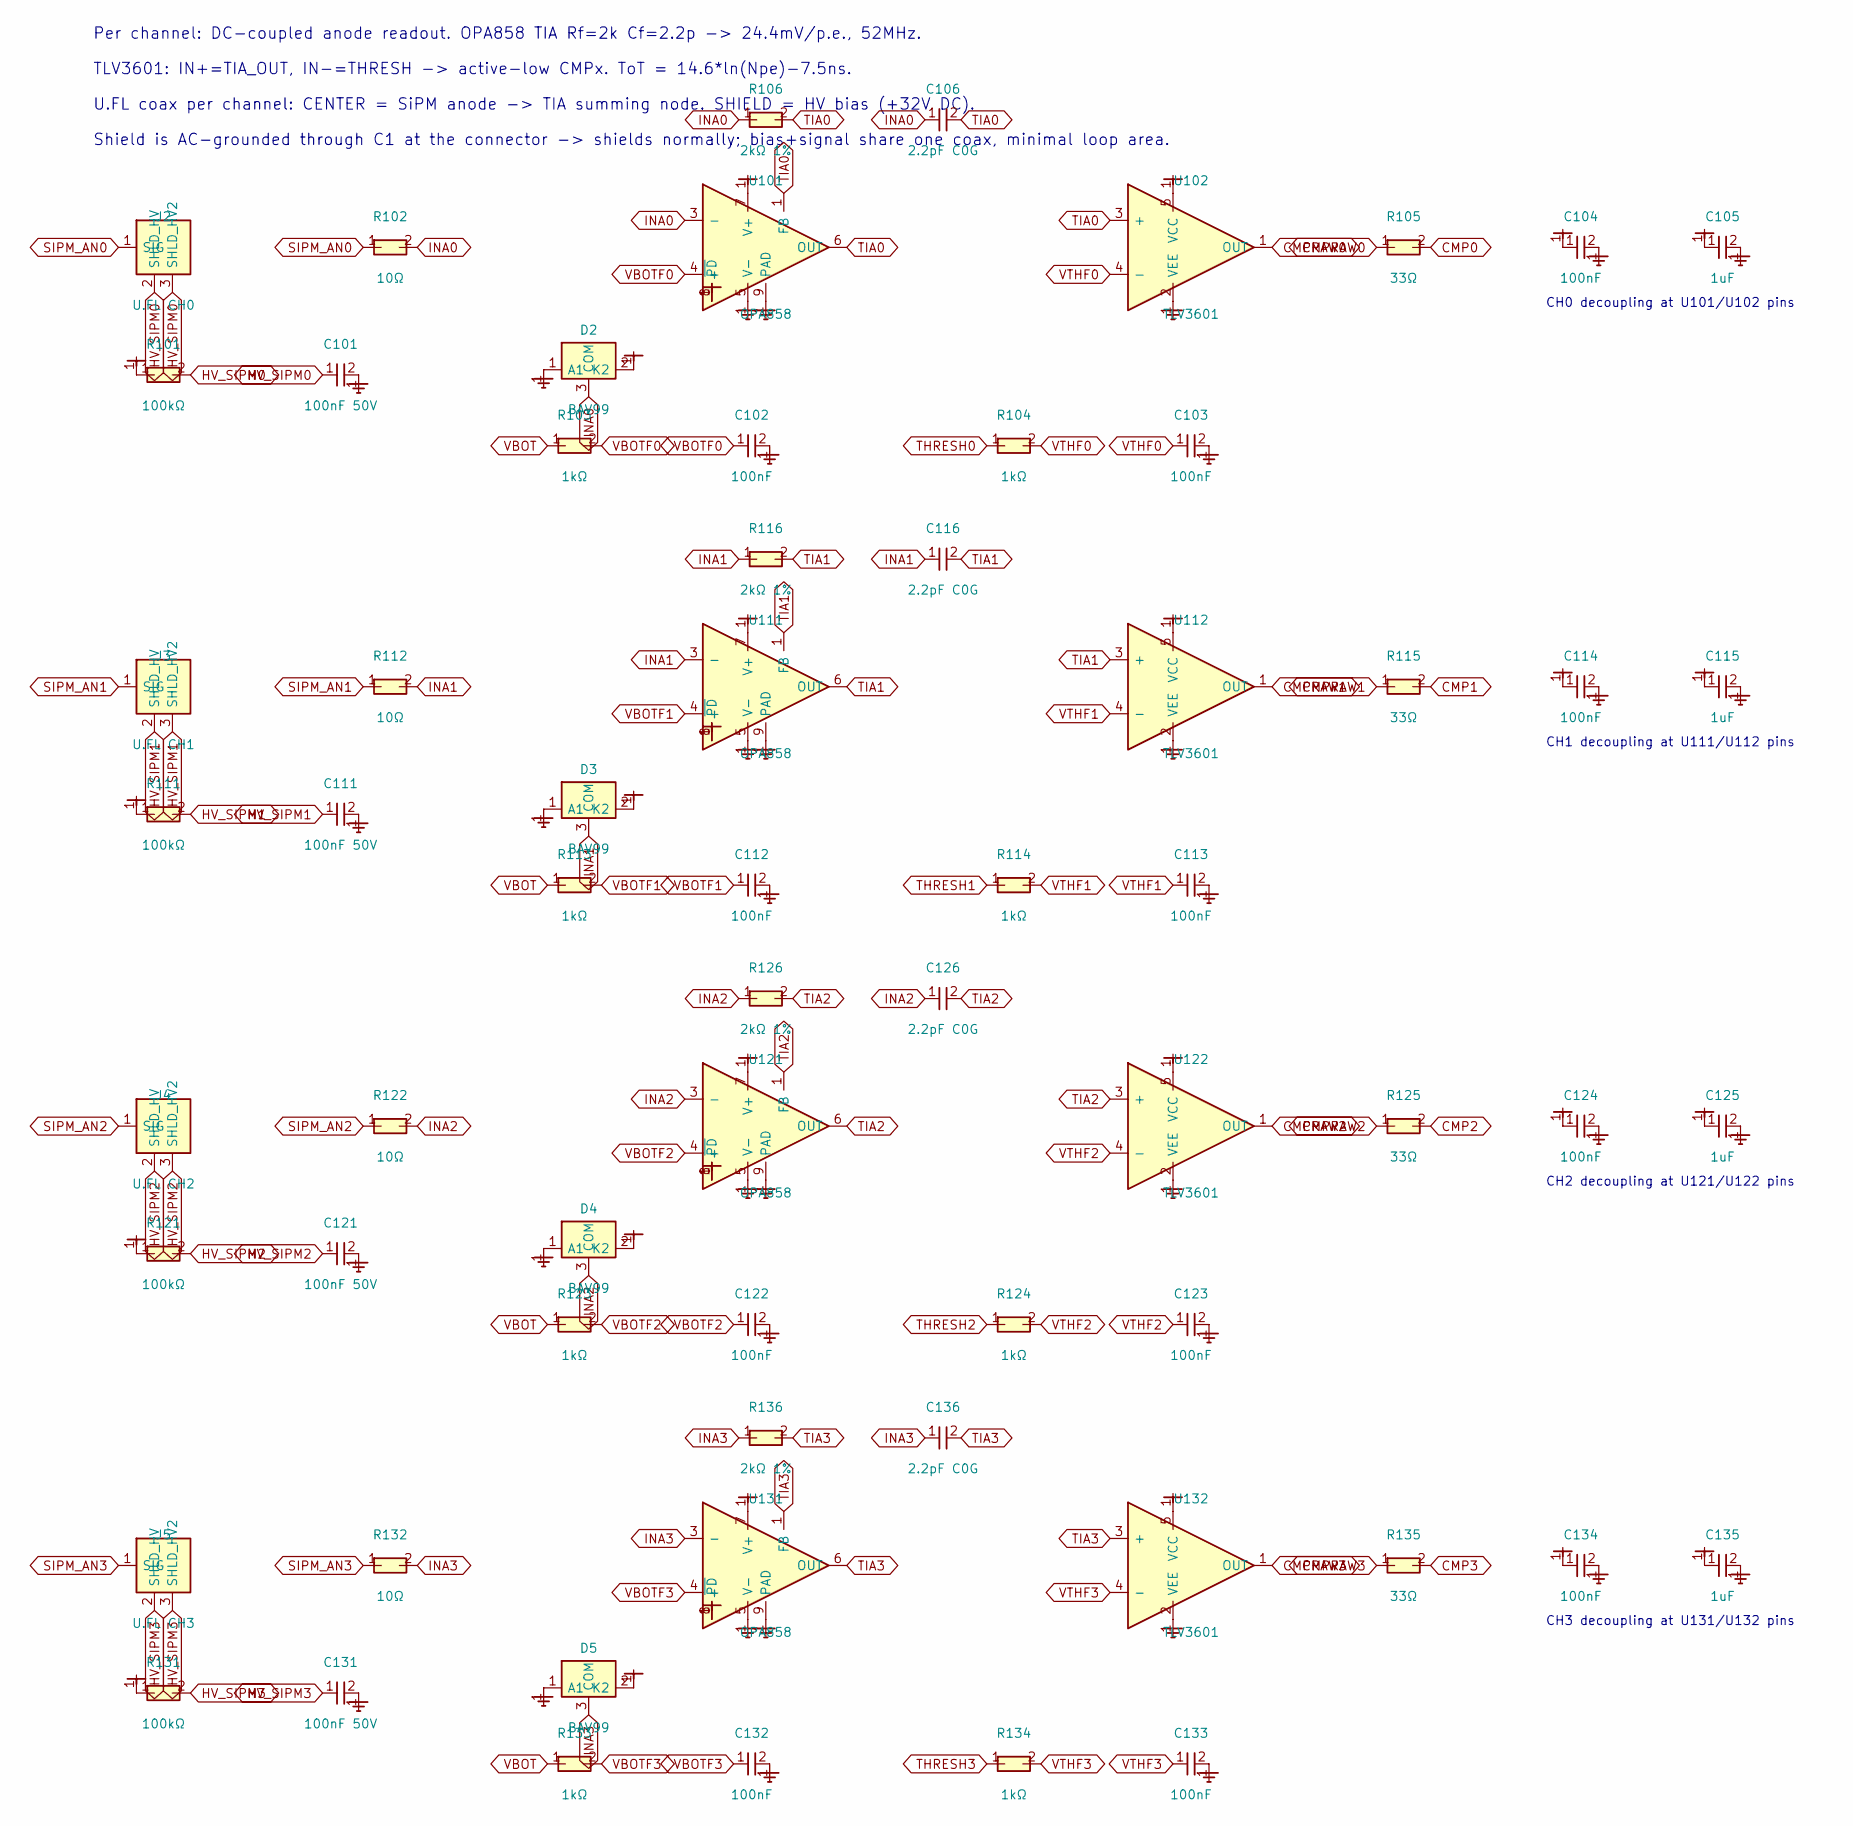
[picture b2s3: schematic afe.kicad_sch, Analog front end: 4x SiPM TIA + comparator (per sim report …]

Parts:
C101, C111, C121, C131: 100nF 50V; C_0805
C102, C103, C104, C112, C113, C114, C122, C123, C124, C132, C133, C134: 100nF; C_0402; LCSC C1525
C105, C115, C125, C135: 1uF; C_0402; LCSC C52923
C106, C116, C126, C136: 2.2pF C0G; C_0402; LCSC C1559
D2, D3, D4, D5: BAV99; SOT-23-3_L2.9-W1.6-P1.90-LS2.8-BR; LCSC C2500
J2: U.FL CH0; IPEX-SMD_BWIPX-1-001E; LCSC C5137195
J3: U.FL CH1; IPEX-SMD_BWIPX-1-001E; LCSC C5137195
J4: U.FL CH2; IPEX-SMD_BWIPX-1-001E; LCSC C5137195
J5: U.FL CH3; IPEX-SMD_BWIPX-1-001E; LCSC C5137195
R101, R111, R121, R131: 100kΩ; R_0402; LCSC C25741
R102, R112, R122, R132: 10Ω; R_0402; LCSC C25077
R103, R104, R113, R114, R123, R124, R133, R134: 1kΩ; R_0402; LCSC C11702
R105, R115, R125, R135: 33Ω; R_0402; LCSC C25105
R106, R116, R126, R136: 2kΩ 1%; R_0402; LCSC C4109
U101, U111, U121, U131: OPA858; WSON-8-1EP_2x2mm_P0.5mm_EP0.9x1.6mm
U102, U112, U122, U132: TLV3601; SOT-23-5

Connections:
+3V3: C104.1, C105.1, C114.1, C115.1, C124.1, C125.1, C134.1, C135.1, D2.2 (K2), D3.2 (K2), D4.2 (K2), D5.2 (K2), U101.7 (V+), U101.8 (~PD), U102.5 (VCC), U111.7 (V+), U111.8 (~PD), U112.5 (VCC), U121.7 (V+), U121.8 (~PD), U122.5 (VCC), U131.7 (V+), U131.8 (~PD), U132.5 (VCC); also elsewhere on the board
CMP0: R105.2; also elsewhere on the board
CMP1: R115.2; also elsewhere on the board
CMP2: R125.2; also elsewhere on the board
CMP3: R135.2; also elsewhere on the board
CMPRAW0: R105.1, U102.1 (OUT)
CMPRAW1: R115.1, U112.1 (OUT)
CMPRAW2: R125.1, U122.1 (OUT)
CMPRAW3: R135.1, U132.1 (OUT)
GND: C101.2, C102.2, C103.2, C104.2, C105.2, C111.2, C112.2, C113.2, C114.2, C115.2, C121.2, C122.2, C123.2, C124.2, C125.2, C131.2, C132.2, C133.2, C134.2, C135.2, D2.1 (A1), D3.1 (A1), D4.1 (A1), D5.1 (A1), U101.5 (V-), U101.9 (PAD), U102.2 (VEE), U111.5 (V-), U111.9 (PAD), U112.2 (VEE), U121.5 (V-), U121.9 (PAD), U122.2 (VEE), U131.5 (V-), U131.9 (PAD), U132.2 (VEE); also elsewhere on the board
HV_QUIET: R101.1, R111.1, R121.1, R131.1; also elsewhere on the board
HV_SIPM0: C101.1, J2.2 (SHLD_HV), J2.3 (SHLD_HV2), R101.2
HV_SIPM1: C111.1, J3.2 (SHLD_HV), J3.3 (SHLD_HV2), R111.2
HV_SIPM2: C121.1, J4.2 (SHLD_HV), J4.3 (SHLD_HV2), R121.2
HV_SIPM3: C131.1, J5.2 (SHLD_HV), J5.3 (SHLD_HV2), R131.2
INA0: C106.1, D2.3 (COM), R102.2, R106.1, U101.3 (-)
INA1: C116.1, D3.3 (COM), R112.2, R116.1, U111.3 (-)
INA2: C126.1, D4.3 (COM), R122.2, R126.1, U121.3 (-)
INA3: C136.1, D5.3 (COM), R132.2, R136.1, U131.3 (-)
SIPM_AN0: J2.1 (SIG), R102.1
SIPM_AN1: J3.1 (SIG), R112.1
SIPM_AN2: J4.1 (SIG), R122.1
SIPM_AN3: J5.1 (SIG), R132.1
THRESH0: R104.1; also elsewhere on the board
THRESH1: R114.1; also elsewhere on the board
THRESH2: R124.1; also elsewhere on the board
THRESH3: R134.1; also elsewhere on the board
TIA0: C106.2, R106.2, U101.1 (FB), U101.6 (OUT), U102.3 (+)
TIA1: C116.2, R116.2, U111.1 (FB), U111.6 (OUT), U112.3 (+)
TIA2: C126.2, R126.2, U121.1 (FB), U121.6 (OUT), U122.3 (+)
TIA3: C136.2, R136.2, U131.1 (FB), U131.6 (OUT), U132.3 (+)
VBOT: R103.1, R113.1, R123.1, R133.1; also elsewhere on the board
VBOTF0: C102.1, R103.2, U101.4 (+)
VBOTF1: C112.1, R113.2, U111.4 (+)
VBOTF2: C122.1, R123.2, U121.4 (+)
VBOTF3: C132.1, R133.2, U131.4 (+)
VTHF0: C103.1, R104.2, U102.4 (-)
VTHF1: C113.1, R114.2, U112.4 (-)
VTHF2: C123.1, R124.2, U122.4 (-)
VTHF3: C133.1, R134.2, U132.4 (-)

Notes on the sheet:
Per channel: DC-coupled anode readout. OPA858 TIA Rf=2k Cf=2.2p -> 24.4mV/p.e., 52MHz.
TLV3601: IN+=TIA_OUT, IN-=THRESH -> active-low CMPx. ToT = 14.6*ln(Npe)-7.5ns.
U.FL coax per channel: CENTER = SiPM anode -> TIA summing node. SHIELD = HV bias (+32V DC).
Shield is AC-grounded through C1 at the connector -> shields normally; bias+signal share one coax, minimal loop area.
CH0 decoupling at U101/U102 pins
CH1 decoupling at U111/U112 pins
CH2 decoupling at U121/U122 pins
CH3 decoupling at U131/U132 pins

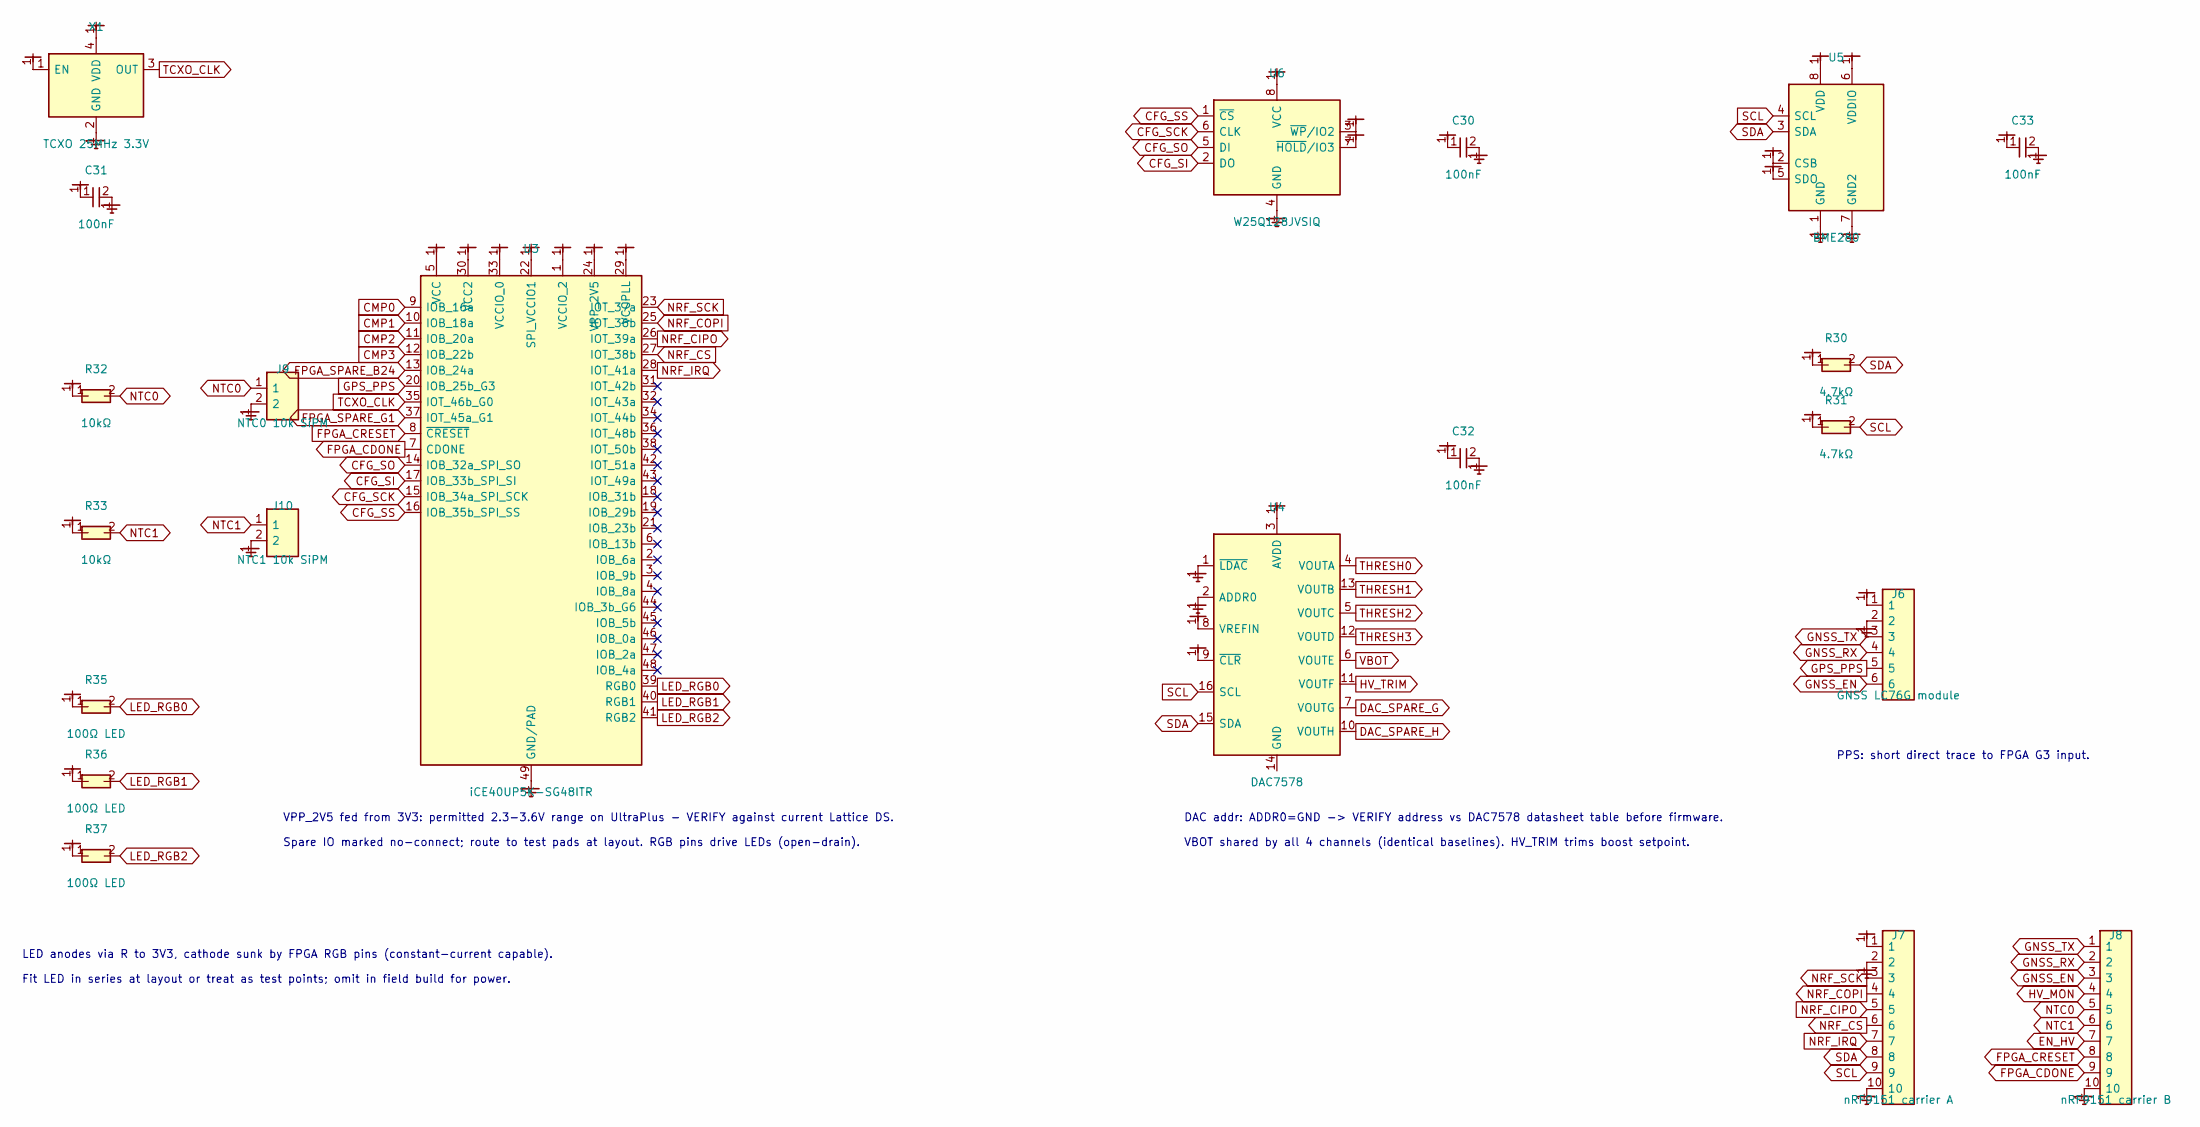
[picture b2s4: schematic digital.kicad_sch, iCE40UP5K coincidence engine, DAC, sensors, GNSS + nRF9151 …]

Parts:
C30, C31, C32, C33: 100nF; C_0402; LCSC C1525
J6: GNSS LC76G module; PinHeader_1x06_P2.54mm_Vertical
J7: nRF9151 carrier A; PinHeader_1x10_P2.54mm_Vertical
J8: nRF9151 carrier B; PinHeader_1x10_P2.54mm_Vertical
J9: NTC0 10k SiPM; PinHeader_1x02_P2.54mm_Vertical
J10: NTC1 10k SiPM; PinHeader_1x02_P2.54mm_Vertical
R30, R31: 4.7kΩ; R_0402; LCSC C25900
R32, R33: 10kΩ; R_0402; LCSC C25744
R35, R36, R37: 100Ω LED; R_0402; LCSC C25076
U3: iCE40UP5K-SG48ITR; QFN-48-1EP_7x7mm_P0.5mm_EP5.6x5.6mm
U4: DAC7578; TSSOP-16_4.4x5mm_P0.65mm
U5: BME280; Bosch_LGA-8_2.5x2.5mm_P0.65mm_ClockwisePinNumbering; LCSC C92489
U6: W25Q128JVSIQ; SOIC-8_L5.3-W5.3-P1.27-LS8.0-BL; LCSC C97521
X1: TCXO 25MHz 3.3V; Oscillator_SMD_ECS_2520MV-xxx-xx-4Pin_2.5x2.0mm

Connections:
+1V2: U3.5 (VCC), U3.30 (VCC2); also elsewhere on the board
+3V3: C30.1, C31.1, C32.1, C33.1, J6.1, R30.1, R31.1, R32.1, R33.1, R35.1, R36.1, R37.1, U3.1 (VCCIO_2), U3.22 (SPI_VCCIO1), U3.24 (VPP_2V5), U3.29 (VCCPLL), U3.33 (VCCIO_0), U4.3 (AVDD), U4.8 (VREFIN), U4.9 (~CLR), U5.2 (CSB), U5.5 (SDO), U5.6 (VDDIO), U5.8 (VDD), U6.3 (~WP/IO2), U6.7 (~HOLD/IO3), U6.8 (VCC), X1.1 (EN), X1.4 (VDD); also elsewhere on the board
CFG_SCK: U3.15 (IOB_34a_SPI_SCK), U6.6 (CLK)
CFG_SI: U3.17 (IOB_33b_SPI_SI), U6.2 (DO)
CFG_SO: U3.14 (IOB_32a_SPI_SO), U6.5 (DI)
CFG_SS: U3.16 (IOB_35b_SPI_SS), U6.1 (~CS)
CMP0: U3.9 (IOB_16a); also elsewhere on the board
CMP1: U3.10 (IOB_18a); also elsewhere on the board
CMP2: U3.11 (IOB_20a); also elsewhere on the board
CMP3: U3.12 (IOB_22b); also elsewhere on the board
DAC_SPARE_G: U4.7 (VOUTG)
DAC_SPARE_H: U4.10 (VOUTH)
EN_HV: J8.7; also elsewhere on the board
FPGA_CDONE: J8.9, U3.7 (CDONE)
FPGA_CRESET: J8.8, U3.8 (~CRESET)
FPGA_SPARE_B24: U3.13 (IOB_24a)
FPGA_SPARE_G1: U3.37 (IOT_45a_G1)
GND: C30.2, C31.2, C32.2, C33.2, J6.2, J7.2, J7.10, J8.10, J9.2, J10.2, U3.49 (GND/PAD), U4.1 (~LDAC), U4.2 (ADDR0), U5.1 (GND), U5.7 (GND2), U6.4 (GND), X1.2 (GND); also elsewhere on the board
GNSS_EN: J6.6, J8.3
GNSS_RX: J6.4, J8.2
GNSS_TX: J6.3, J8.1
GPS_PPS: J6.5, U3.20 (IOB_25b_G3)
HV_MON: J8.4; also elsewhere on the board
HV_TRIM: U4.11 (VOUTF); also elsewhere on the board
LED_RGB0: R35.2, U3.39 (RGB0)
LED_RGB1: R36.2, U3.40 (RGB1)
LED_RGB2: R37.2, U3.41 (RGB2)
NRF_CIPO: J7.5, U3.26 (IOT_39a)
NRF_COPI: J7.4, U3.25 (IOT_36b)
NRF_CS: J7.6, U3.27 (IOT_38b)
NRF_IRQ: J7.7, U3.28 (IOT_41a)
NRF_SCK: J7.3, U3.23 (IOT_37a)
NTC0: J8.5, J9.1, R32.2
NTC1: J8.6, J10.1, R33.2
SCL: J7.9, R31.2, U4.16 (SCL), U5.4 (SCL)
SDA: J7.8, R30.2, U4.15 (SDA), U5.3 (SDA)
TCXO_CLK: U3.35 (IOT_46b_G0), X1.3 (OUT)
THRESH0: U4.4 (VOUTA); also elsewhere on the board
THRESH1: U4.13 (VOUTB); also elsewhere on the board
THRESH2: U4.5 (VOUTC); also elsewhere on the board
THRESH3: U4.12 (VOUTD); also elsewhere on the board
VBOT: U4.6 (VOUTE); also elsewhere on the board
VSYS: J7.1; also elsewhere on the board

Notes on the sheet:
VPP_2V5 fed from 3V3: permitted 2.3-3.6V range on UltraPlus - VERIFY against current Lattice DS.
Spare IO marked no-connect; route to test pads at layout. RGB pins drive LEDs (open-drain).
DAC addr: ADDR0=GND -> VERIFY address vs DAC7578 datasheet table before firmware.
VBOT shared by all 4 channels (identical baselines). HV_TRIM trims boost setpoint.
PPS: short direct trace to FPGA G3 input.
LED anodes via R to 3V3, cathode sunk by FPGA RGB pins (constant-current capable).
Fit LED in series at layout or treat as test points; omit in field build for power.

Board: 4 copper layers, 111 parts (0 on the bottom side), 75 nets, no tracks yet.

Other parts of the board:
H1, H2, H3, H4: M3; MountingHole_3.2mm_M3

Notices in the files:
README.md:
License:
See [LICENSE](LICENSE). Third-party datasheets and 3D models belong to their manufacturers. They are fetched on demand
(`cd hw && bun run parts`), not redistributed.
